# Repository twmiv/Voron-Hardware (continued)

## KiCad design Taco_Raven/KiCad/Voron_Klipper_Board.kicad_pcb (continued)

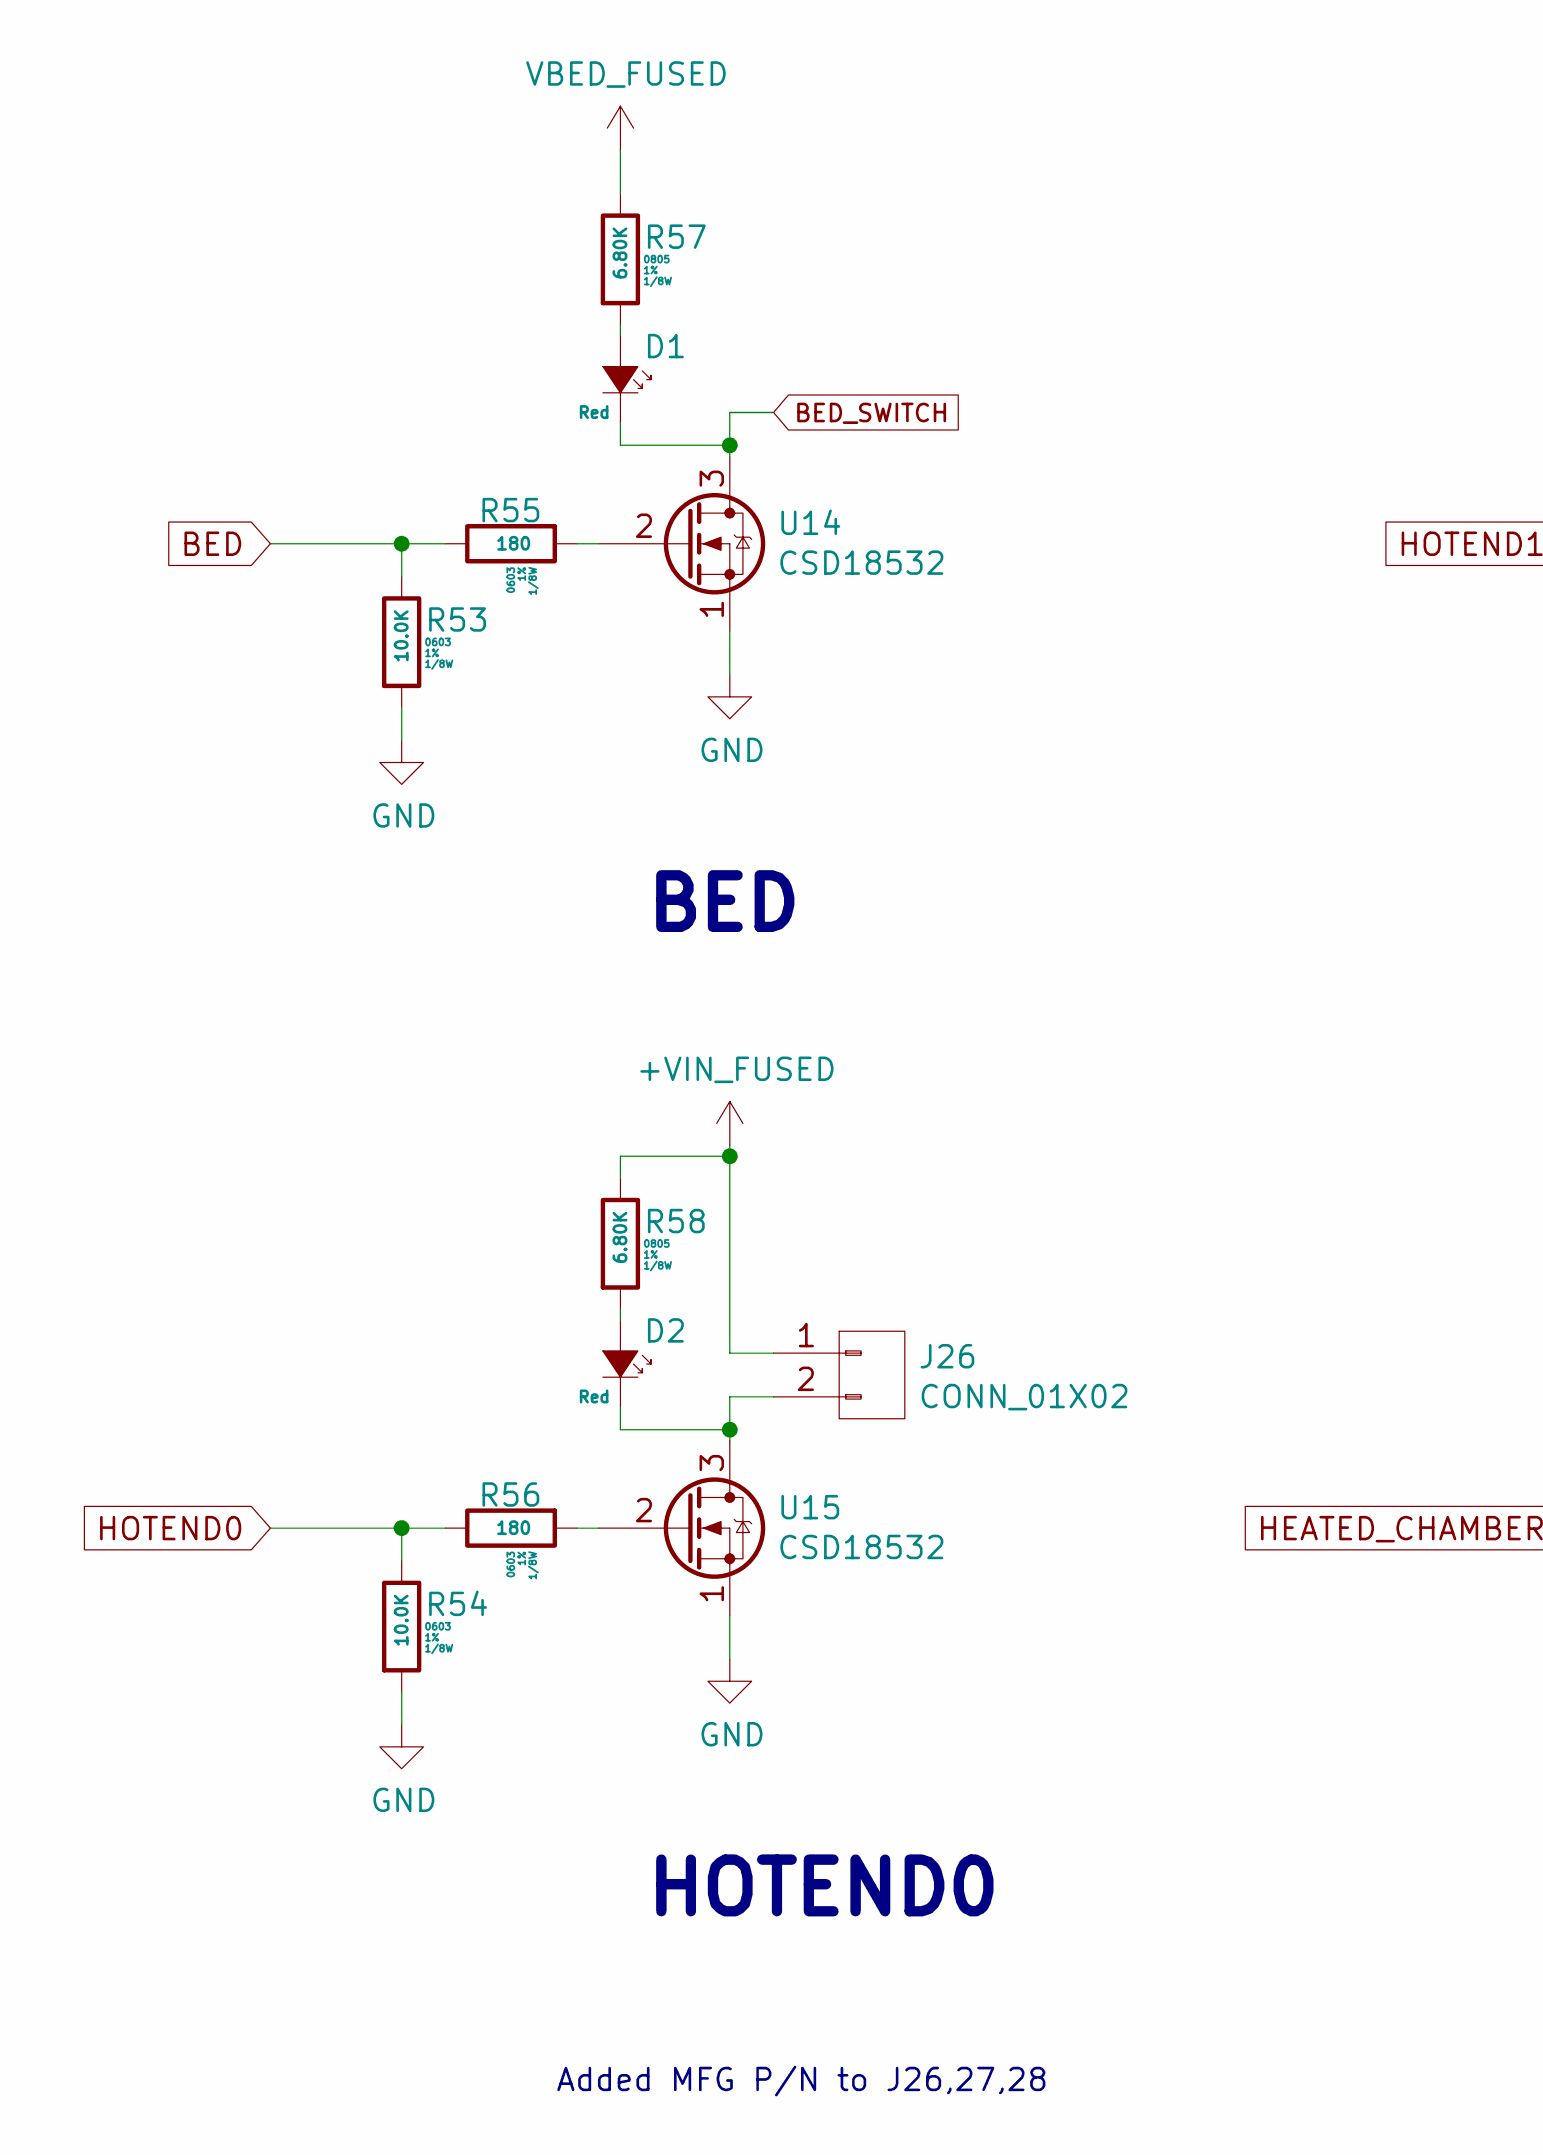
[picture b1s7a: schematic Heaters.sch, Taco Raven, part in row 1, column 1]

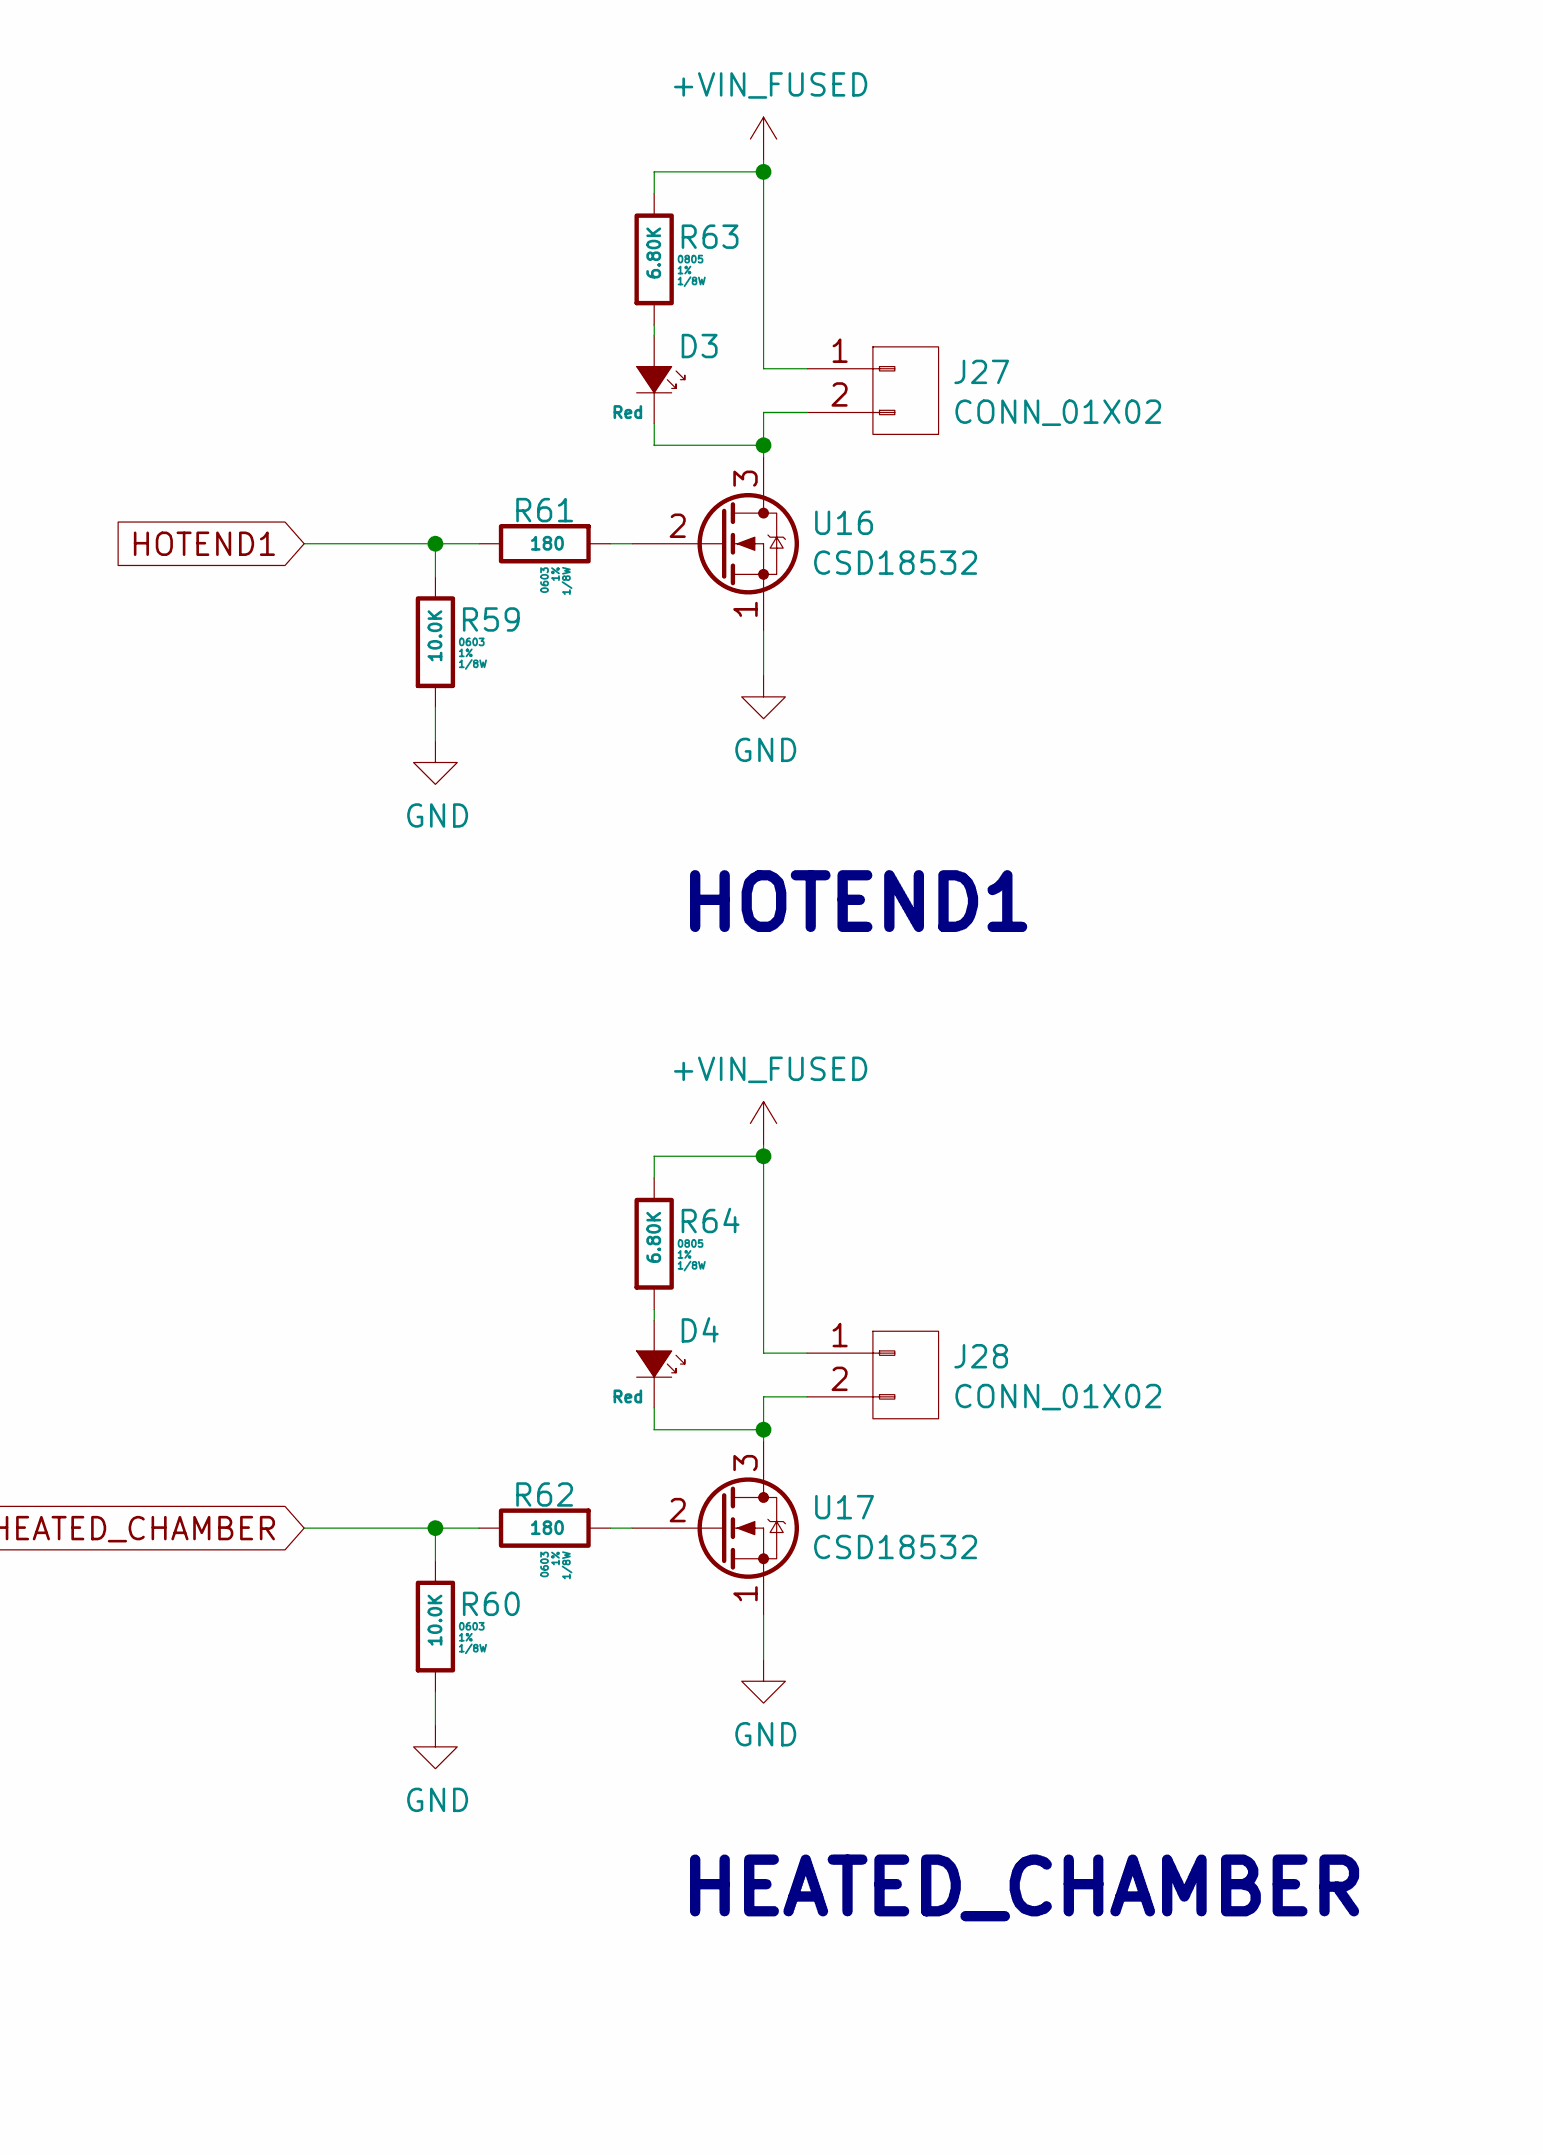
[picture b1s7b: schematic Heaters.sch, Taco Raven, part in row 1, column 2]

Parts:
D1, D2, D3, D4: Red; LED_0805; MFG PN 150080SS75000; Digikey P/N 732-4985-1-ND
J26, J27, J28: CONN_01X02; TerminalBlock_TE_282834-2_1x02_P2.54mm_Horizontal; MFG PN 282834-2; Digikey P/N A98333-ND
R53, R54, R59, R60: 10.0K; R_0603; Tolerance 1%; MFG PN RNCP0603FTD10K0; Digikey P/N RNCP0603FTD10K0CT-ND
R55, R56, R61, R62: 180; R_0603; Tolerance 1%; MFG PN RNCP0603FTD180R; Digikey P/N RNCP0603FTD180RCT-ND
R57, R58, R63, R64: 6.80K; R_0805; Tolerance 1%; MFG PN RMCF0805FT6K80; Digikey P/N RMCF0805FT6K80CT-ND
U14, U15, U16, U17: CSD18532; VSONP-8-1EP_5x6_P1.27mm; MFG PN CSD18532Q5B; Digikey P/N 296-35628-6-ND

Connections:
+VIN_FUSED: J26.1, J27.1, J28.1, R58.1, R63.1, R64.1; also elsewhere on the board
BED: R53.1, R55.1; also elsewhere on the board
BED_SWITCH: D1.1 (K), U14.3; also elsewhere on the board
GND: R53.2, R54.2, R59.2, R60.2, U14.1, U15.1, U16.1, U17.1; also elsewhere on the board
HEATED_CHAMBER: R60.1, R62.1; also elsewhere on the board
HOTEND0: R54.1, R56.1; also elsewhere on the board
HOTEND1: R59.1, R61.1; also elsewhere on the board
unnamed: D1.2 (A), R57.2
unnamed: D2.1 (K), J26.2, U15.3
unnamed: D2.2 (A), R58.2
unnamed: D3.1 (K), J27.2, U16.3
unnamed: D3.2 (A), R63.2
unnamed: D4.1 (K), J28.2, U17.3
unnamed: D4.2 (A), R64.2
unnamed: R55.2, U14.2
unnamed: R56.2, U15.2
unnamed: R61.2, U16.2
unnamed: R62.2, U17.2
VBED_FUSED: R57.1; also elsewhere on the board

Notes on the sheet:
BED
HOTEND0
HOTEND1
HEATED_CHAMBER
Added MFG P/N to J26,27,28

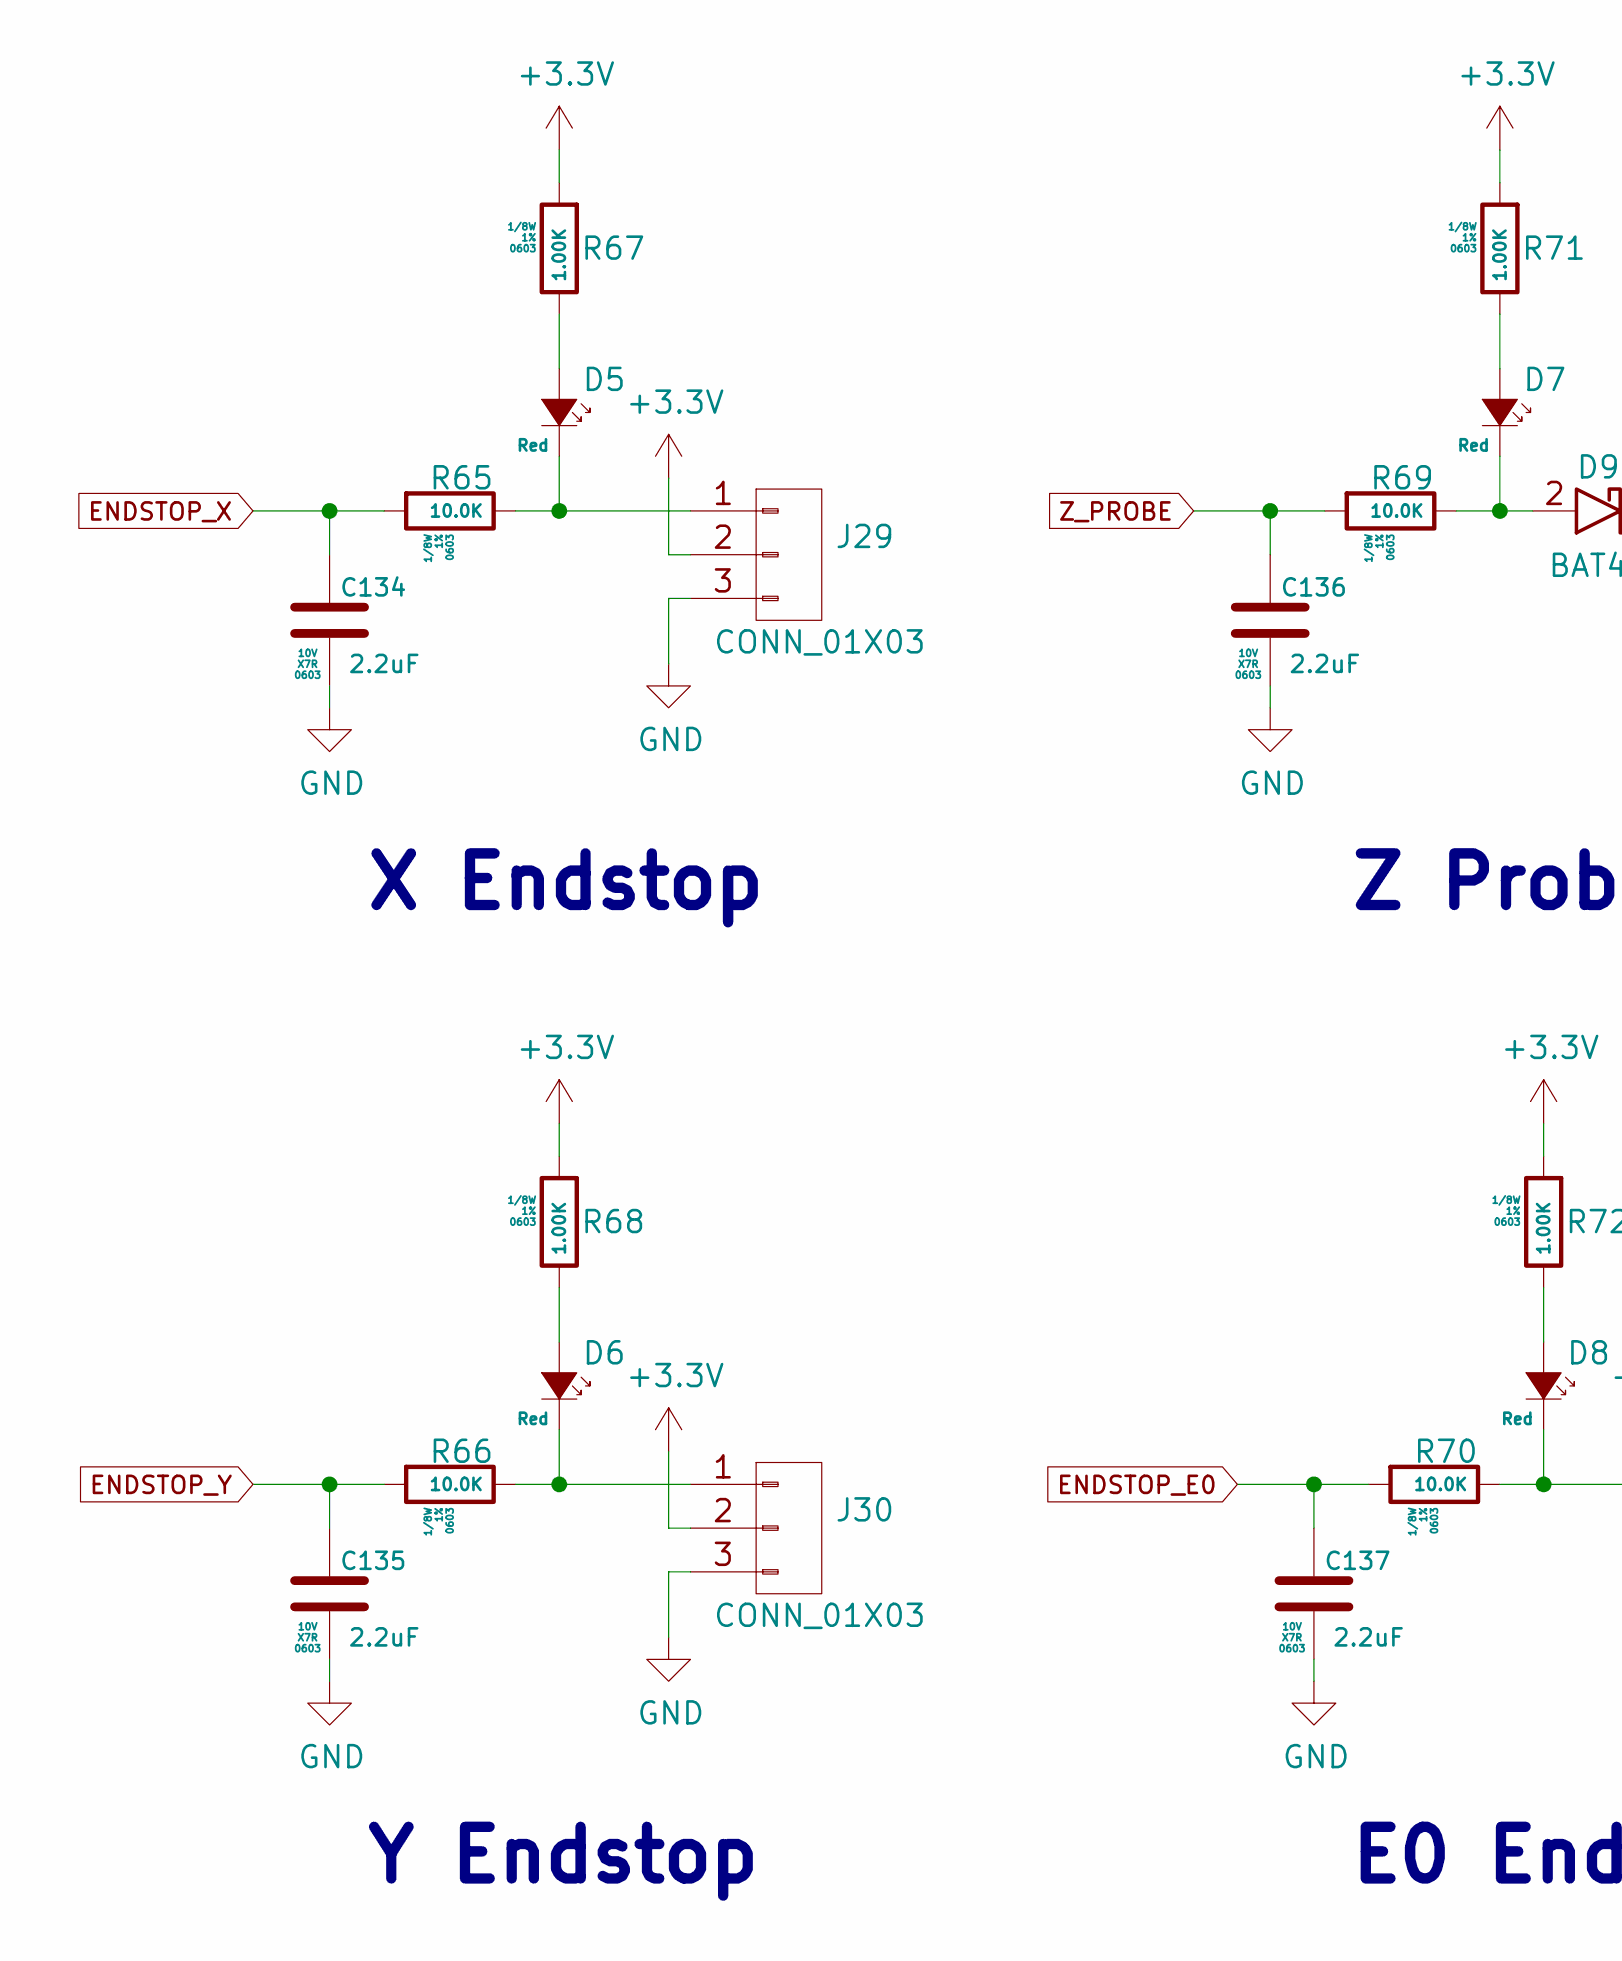
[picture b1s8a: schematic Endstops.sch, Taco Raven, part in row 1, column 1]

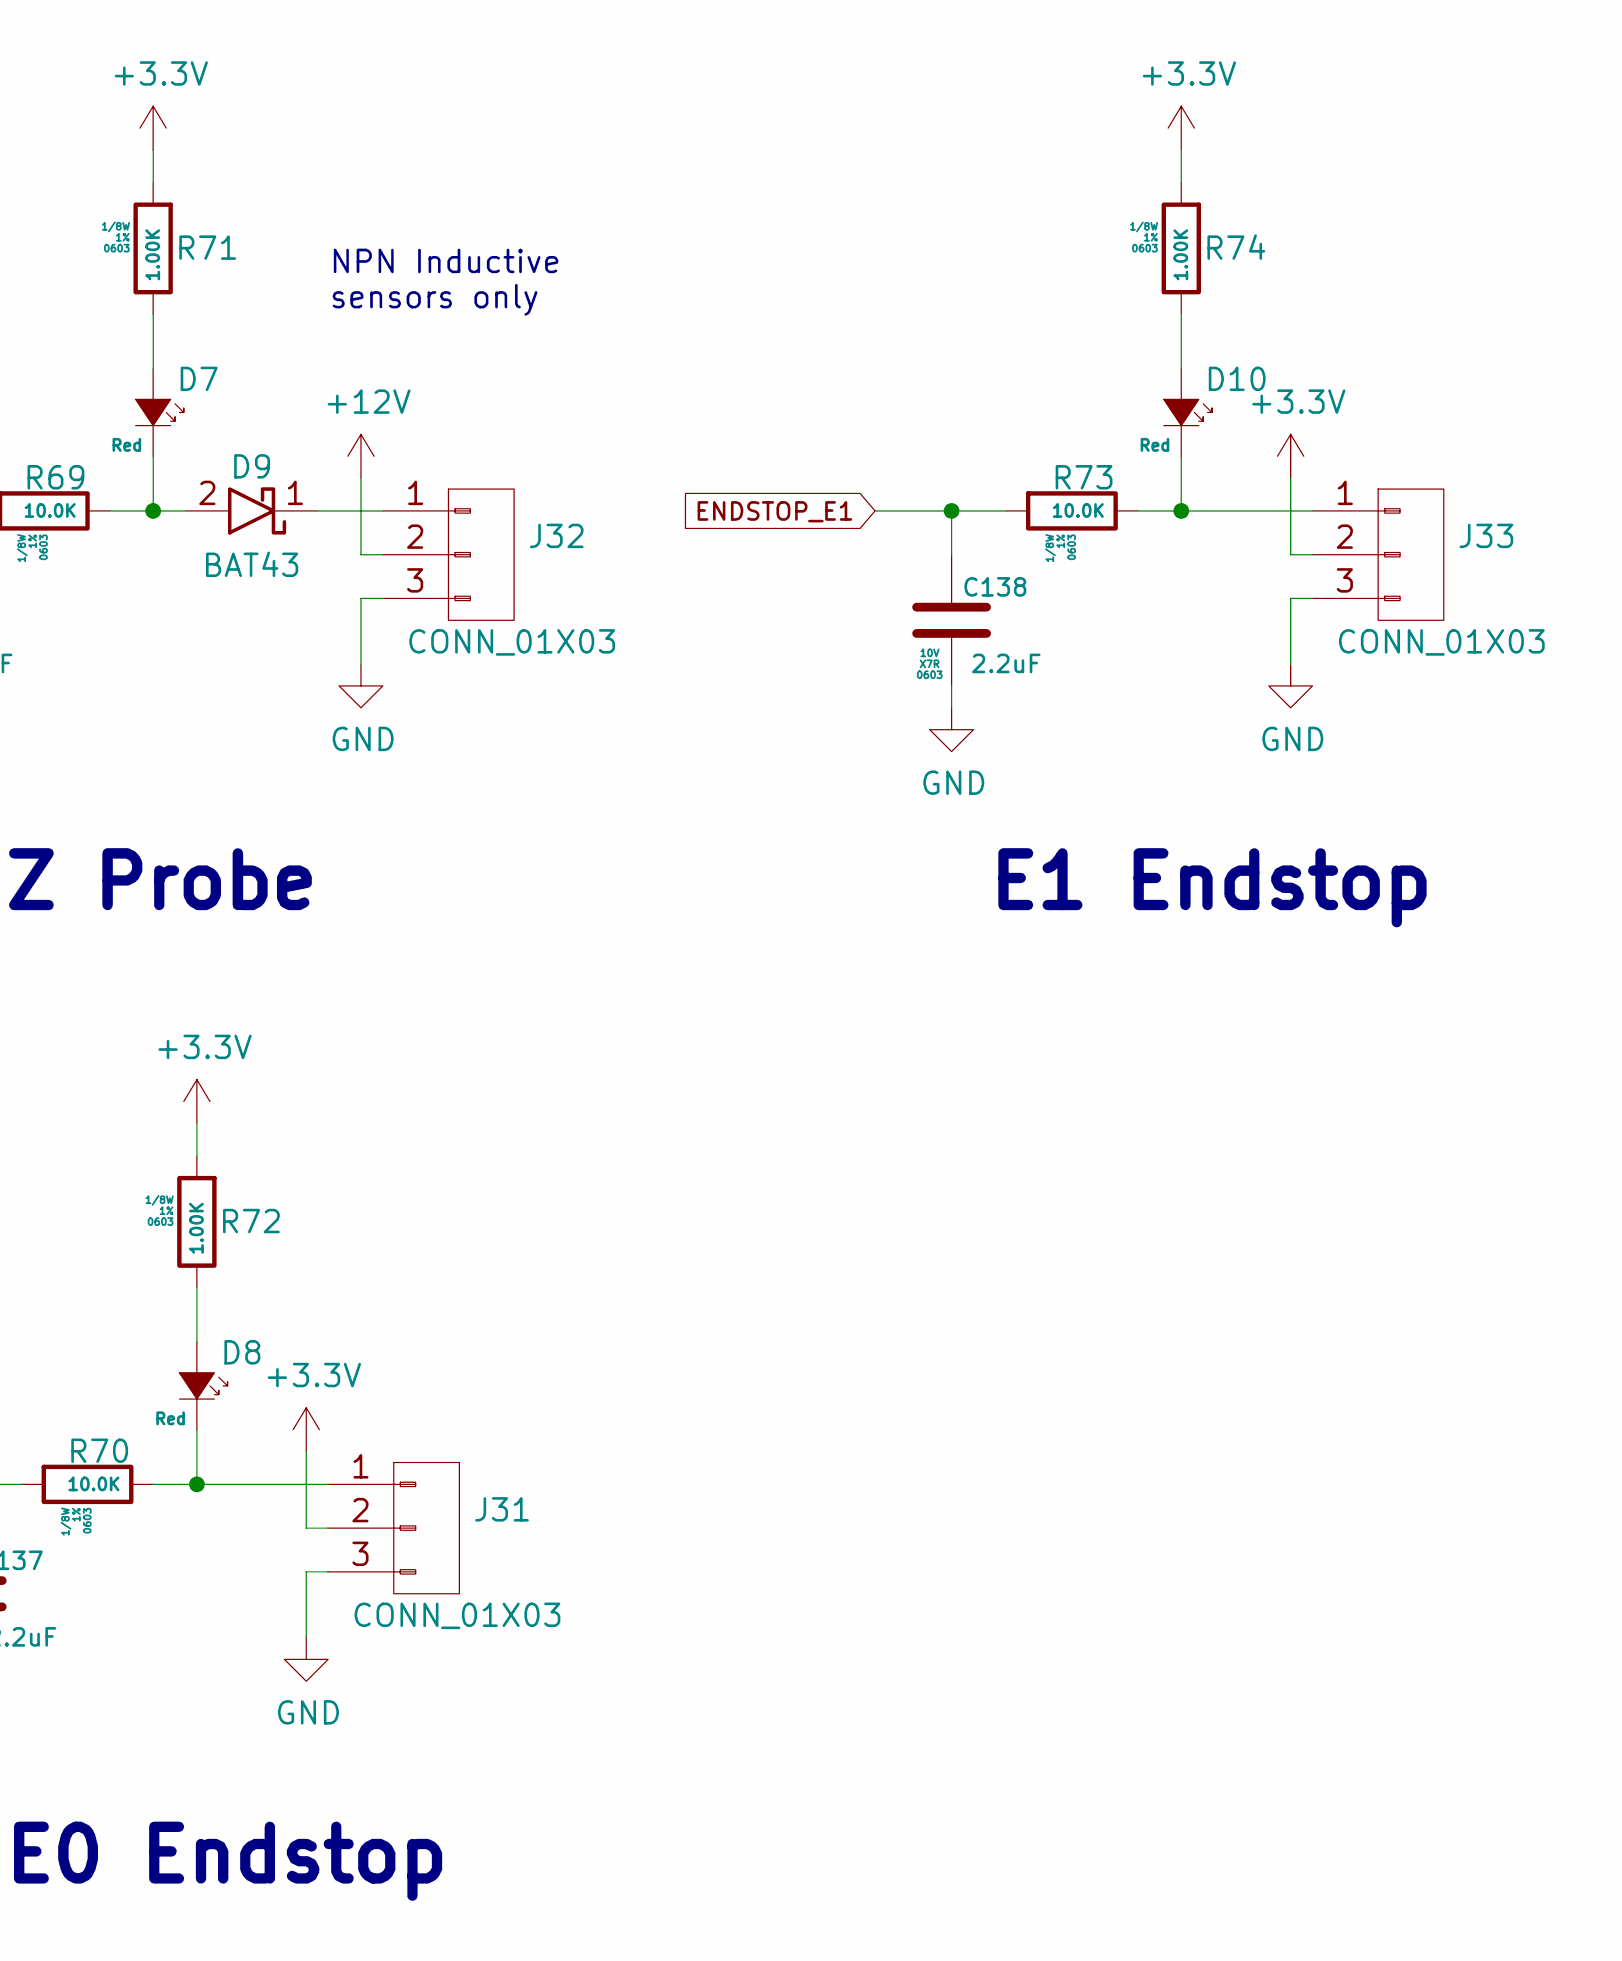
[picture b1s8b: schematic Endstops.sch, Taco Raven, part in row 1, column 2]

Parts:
C134, C135, C136, C137, C138: 2.2uF; C_0603; Voltage 10V; MFG PN LMK107B7225KA-T; Digikey P/N 587-2983-1-ND
D5, D6, D7, D8, D10: Red; LED_0805; MFG PN 150080SS75000; Digikey P/N 732-4985-1-ND
D9: BAT43; D_SOD-323; MFG PN BAT43WS-7-F; Digikey P/N BAT43WS-FDICT-ND
J29, J30, J31, J32, J33: CONN_01X03; Molex_KK_1X3; MFG PN 0022232031; Digikey P/N WM4201-ND
R65, R66, R69, R70, R73: 10.0K; R_0603; Tolerance 1%; MFG PN RNCP0603FTD10K0; Digikey P/N RNCP0603FTD10K0CT-ND
R67, R68, R71, R72, R74: 1.00K; R_0603; Tolerance 1%; MFG PN RNCP0603FTD1K00; Digikey P/N RNCP0603FTD1K00CT-ND

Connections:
+3.3V: J29.2, J30.2, J31.2, J33.2, R67.2, R68.2, R71.2, R72.2, R74.2; also elsewhere on the board
+12V: J32.2; also elsewhere on the board
ENDSTOP_E0: C137.2, R70.2; also elsewhere on the board
ENDSTOP_E1: C138.2, R73.2; also elsewhere on the board
ENDSTOP_X: C134.2, R65.2; also elsewhere on the board
ENDSTOP_Y: C135.2, R66.2; also elsewhere on the board
GND: C134.1, C135.1, C136.1, C137.1, C138.1, J29.3, J30.3, J31.3, J32.3, J33.3; also elsewhere on the board
unnamed: D5.1 (K), J29.1, R65.1
unnamed: D5.2 (A), R67.1
unnamed: D6.1 (K), J30.1, R66.1
unnamed: D6.2 (A), R68.1
unnamed: D7.1 (K), D9.2, R69.1
unnamed: D7.2 (A), R71.1
unnamed: D8.1 (K), J31.1, R70.1
unnamed: D8.2 (A), R72.1
unnamed: D9.1, J32.1
unnamed: D10.1 (K), J33.1, R73.1
unnamed: D10.2 (A), R74.1
Z_PROBE: C136.2, R69.2; also elsewhere on the board

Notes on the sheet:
X Endstop
Z Probe
E1 Endstop
Y Endstop
E0 Endstop
NPN Inductive sensors only

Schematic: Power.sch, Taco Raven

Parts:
C113, C114, C139, C140, C141, C142, C143, C144, C153, C154, C155, C156: 100nF; C_0603; Voltage 50V; MFG PN CC0603KRX7R9BB104; Digikey P/N 311-1344-1-ND
C145, C148: 1uF; C_0603; Voltage 10V; MFG PN CL10B105KP8NNNC; Digikey P/N 1276-1946-1-ND
C146, C147: 10uF; C_0805; Voltage 16V; MFG PN CL21A106KOQNNWE; Digikey P/N 1276-2894-1-ND
C149, C150: 100uF; CP_Elec_6.3x7.7; Voltage 50V; MFG PN EMZR500ARA101MF80G; Digikey P/N 565-5153-1-ND
C151, C152, C159, C160, C161, C162: 10uF; C_1210; Voltage 35V; MFG PN C1210C106M6PACTU; Digikey P/N 399-5509-1-ND
C157, C158: 22nF; C_0603; Voltage 50V; MFG PN CL10B223KB8WPNC; Digikey P/N 311-3601-1-ND
C163: 8.2nF; C_0603; Voltage 50V; MFG PN C1608C0G1H822K080AA; Digikey P/N 445-13992-6-ND
C164: 10nF; C_0603; Voltage 50V; MFG PN 06035C103KAT2A; Digikey P/N 478-1227-1-ND
D11, D12, D13, D14: Blue; LED_0805; MFG PN 150080BS75000; Digikey P/N 732-4982-1-ND
D15, D16, D17, D18, D19: DB2W40300L; D_SOD-123F; MFG PN DB2W40300L; Digikey P/N DB2W40300LCT-ND
F1, F2, F3: 3557-2; Fuseholder_Blade_Mini_Keystone_3568; MFG PN 3557-2; Digikey P/N 36-3557-2-ND
J25: CONN_01X06; 8PCV-06-006; MFG PN 8PCV-06-006; Digikey P/N A98464-ND
L3, L4: 10uH; L_Vishay_IHLP-2525; MFG PN IHLP2525CZER100M11; Digikey P/N 541-2581-1-ND
R75, R76: 6.80K; R_0805; Tolerance 1%; MFG PN RMCF0805FT6K80; Digikey P/N RMCF0805FT6K80CT-ND
R77: 1.00K; R_0603; Tolerance 1%; MFG PN RNCP0603FTD1K00; Digikey P/N RNCP0603FTD1K00CT-ND
R78: 180; R_0603; Tolerance 1%; MFG PN RNCP0603FTD180R; Digikey P/N RNCP0603FTD180RCT-ND
R79, R80: 0R; R_0603; Tolerance 1%; MFG PN RC0603JR-070RL; Digikey P/N 311-0.0GRCT-ND
R81: 200K; R_0603; Tolerance 1%; MFG PN ERJ-3EKF2003V; Digikey P/N P200KHCT-ND
R82, R94, R95, R96: 100K; R_0603; Tolerance 1%; MFG PN ERJ-3EKF1003V; Digikey P/N P100KHCT-ND
R83, R85: 0.10; R_1206; Tolerance 1%; MFG PN CSR1206FTR100; Digikey P/N CSR1206FTR100CT-ND
R84, R86: 0.130; R_1206; Tolerance 1%; MFG PN CSR1206FTR130; Digikey P/N CSR1206FTR130CT-ND
R87: 10.5K; R_0603; Tolerance 1%; MFG PN ERJ-3EKF1052V; Digikey P/N P10.5KHCT-ND
R88: 750; R_0603; Tolerance 1%; MFG PN RNCP0603FTD750R; Digikey P/N RNCP0603FTD750RCT-ND
R89: 3.48K; R_0603; Tolerance 1%; MFG PN ERA-3AEB3481V; Digikey P/N P3.48KDBTR-ND
R90: 681; R_0603; Tolerance 1%; MFG PN RNCP0603FTD681R; Digikey P/N RNCP0603FTD681RCT-ND
U18: AP2112-3.3; SOT-23-5; MFG PN AP2112K-3.3TRG1; Digikey P/N AP2112K-3.3TRG1DICT-ND
U19, U20: A4403; WQFN-16-1EP_4x4mm_P0.65mm_EP2.1x2.1mm_ThermalVias; MFG PN A4403GEUTR-T; Digikey P/N 620-1273-1-ND
U23: PMV40UN; SOT-23; MFG PN PMV40UN2R; Digikey P/N 1727-1900-1-ND

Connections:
+3.3V: C146.2, C148.2, R78.1, U18.5 (VO); also elsewhere on the board
+5V: C114.2, C160.1, C162.1, C164.2, L4.2, R77.1, R89.1, R95.1, U23.2; also elsewhere on the board
+12V: C113.2, C159.1, C161.1, C163.2, L3.2, R76.1, R87.1, R94.2; also elsewhere on the board
+VIN: C140.2, C141.2, F2.1, F3.1, J25.3, R75.1
+VIN_FUSED: C143.2, D15.2, D16.2, F2.2; also elsewhere on the board
BED_SWITCH: J25.6; also elsewhere on the board
GND: C113.1, C114.1, C139.1, C140.1, C141.1, C142.1, C143.1, C144.1, C145.1, C146.1, C147.1, C148.1, C149.2, C150.2, C151.2, C152.2, C153.1, C154.1, C155.1, C156.1, C159.2, C160.2, C161.2, C162.2, D11.1 (K), D12.1 (K), D13.1 (K), D14.1 (K), J25.2, J25.4, R79.2, R80.2, R83.2, R84.2, R85.2, R86.2, R88.2, R90.2, U18.2 (GND), U19.2 (NC), U19.6 (GND), U19.7 (NC), U19.9 (SGND), U19.13 (NC), U19.14 (NC), U19.15 (NC), U19.16 (NC), U19.17 (GPAD), U20.2 (NC), U20.6 (GND), U20.7 (NC), U20.9 (SGND), U20.13 (NC), U20.14 (NC), U20.15 (NC), U20.16 (NC), U20.17 (GPAD); also elsewhere on the board
unnamed: C145.2, C147.2, D19.1, R96.2, U18.1 (VI), U23.3
unnamed: C149.1, C151.1, C153.2, D15.1, R81.1, U19.1 (VIN)
unnamed: C150.1, C152.1, C154.2, D16.1, R82.1, U20.1 (VIN)
unnamed: C155.2, U19.4 (SS)
unnamed: C156.2, U20.4 (SS)
unnamed: C157.1, U19.11 (BOOT)
unnamed: C157.2, D17.1, L3.1, U19.12 (LX)
unnamed: C158.1, U20.11 (BOOT)
unnamed: C158.2, D18.1, L4.1, U20.12 (LX)
unnamed: C163.1, R87.2, R88.1, U19.5 (FB)
unnamed: C164.1, R89.2, R90.1, U20.5 (FB)
unnamed: D11.2 (A), R75.2
unnamed: D12.2 (A), R76.2
unnamed: D13.2 (A), R77.2
unnamed: D14.2 (A), R78.2
unnamed: D17.2, R83.1, R85.1, U19.8 (ISEN)
unnamed: D18.2, R84.1, R86.1, U20.8 (ISEN)
unnamed: R79.1, U19.10 (DIS)
unnamed: R80.1, U20.10 (DIS)
unnamed: R81.2, U19.3 (TON)
unnamed: R82.2, U20.3 (TON)
unnamed: R94.1, R95.2, U23.1
unnamed: R96.1, U18.3 (EN)
VBED_FUSED: C144.2, F3.2, J25.5; also elsewhere on the board
VBUS: D19.2; also elsewhere on the board
VMOT: C139.2, F1.1, J25.1
VMOT_FUSED: C142.2, F1.2; also elsewhere on the board

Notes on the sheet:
Power Terminal
FUSE HOLDER
600mA Max!
Updated R81 from 100k to 200k
Updated R163 from 100nF to 8.2nF
Updated R164 from 100nF to 100nF
Updated R89 from 3.6k to 3.48k

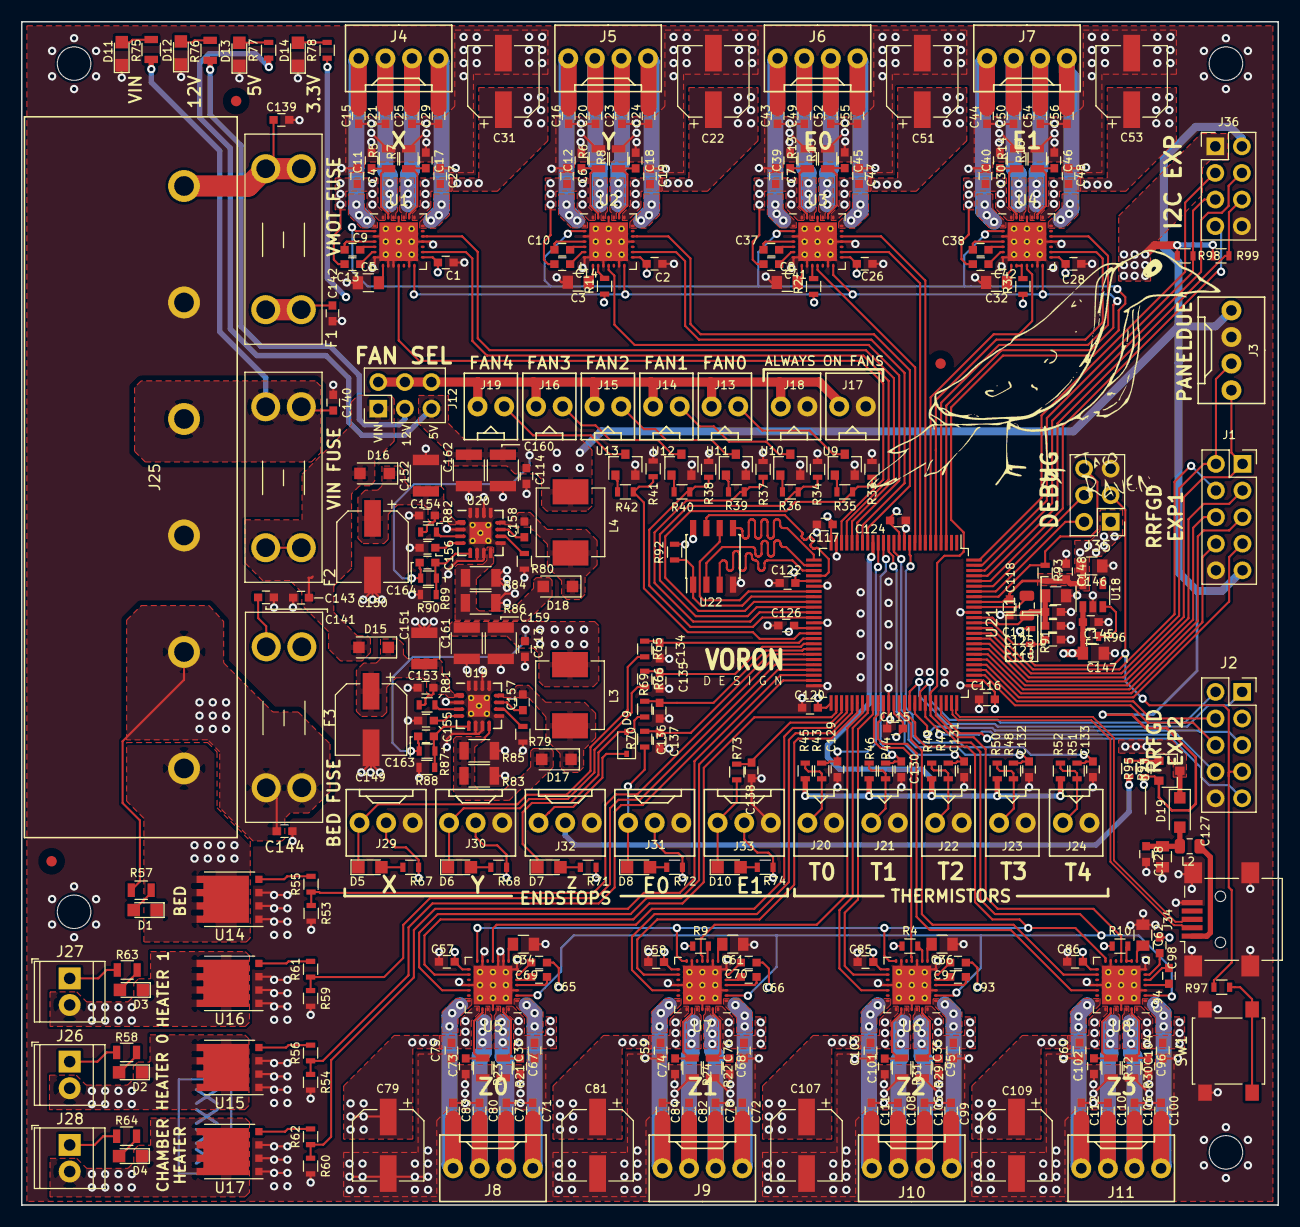
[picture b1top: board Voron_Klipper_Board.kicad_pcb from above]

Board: 4 copper layers, 120.0 x 113.0 mm, 340 parts (0 on the bottom side), 241 nets.

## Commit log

2020-05-12 Add initial symbol for TMC2209
2020-08-16 TMC2209 upgrade layout ready for review
2020-08-16 add gitignore for the project
2020-08-16 apply gitignore
